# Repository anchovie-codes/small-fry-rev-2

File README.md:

# small-fry-rev-2
a keyboard with a fishy layout. now with better mods and a funky pcb!

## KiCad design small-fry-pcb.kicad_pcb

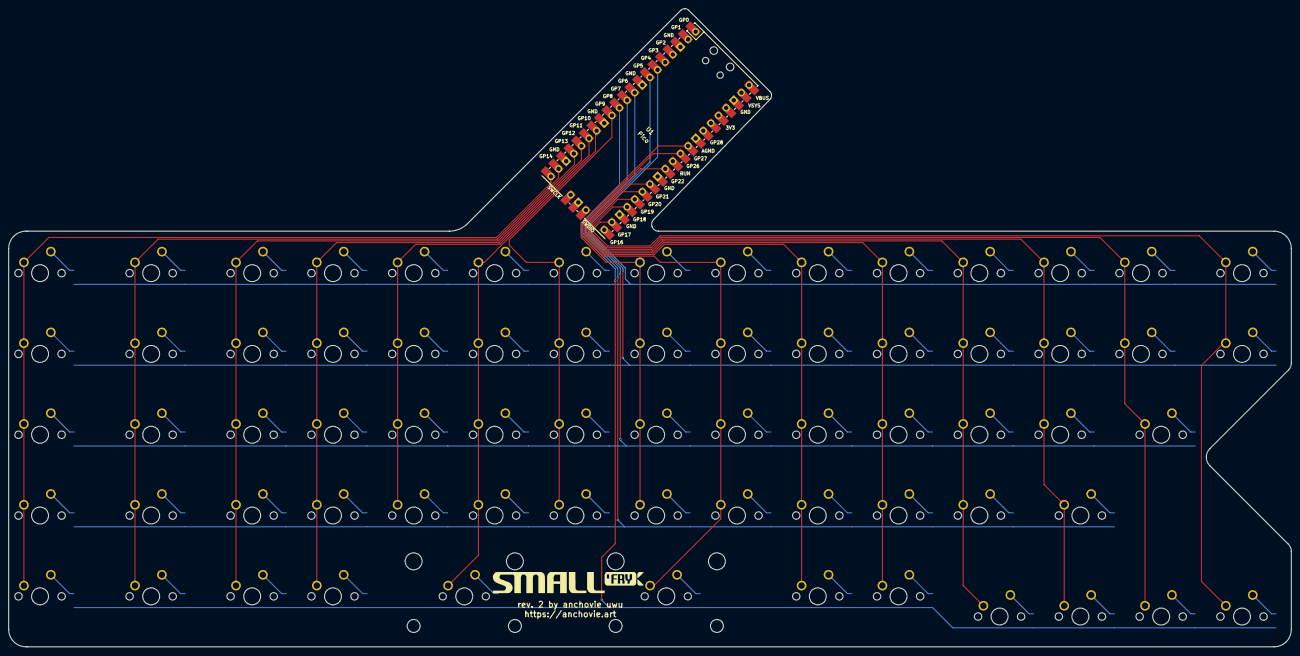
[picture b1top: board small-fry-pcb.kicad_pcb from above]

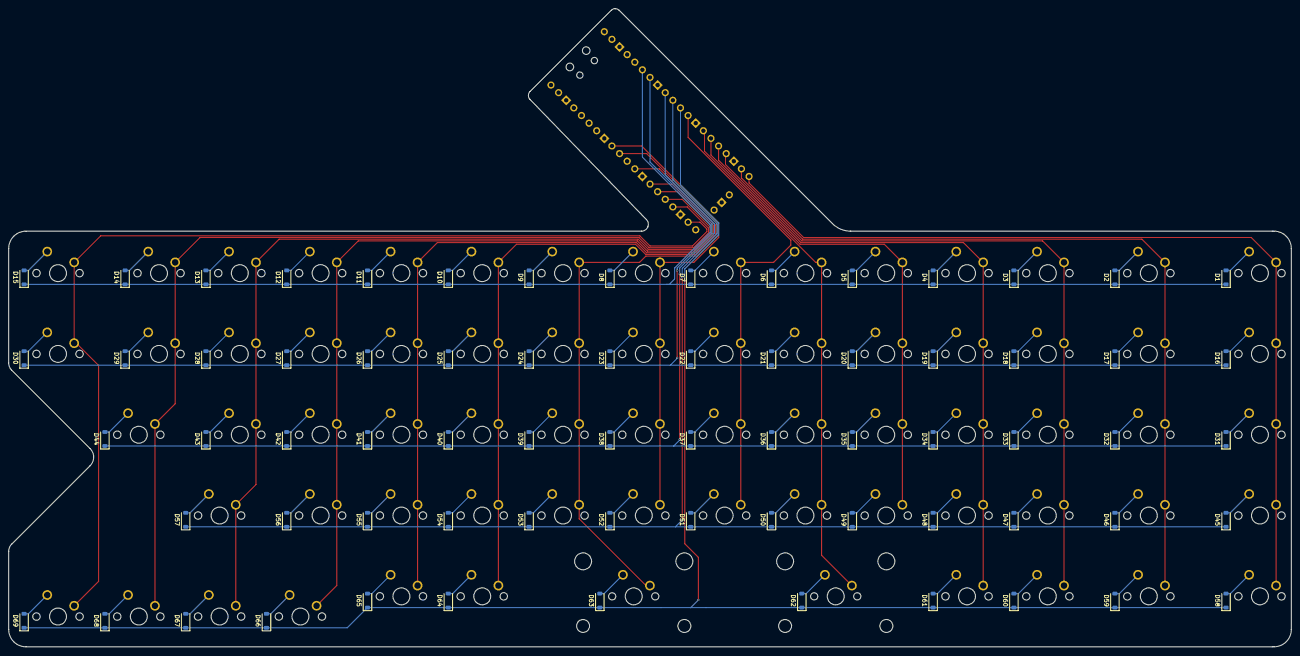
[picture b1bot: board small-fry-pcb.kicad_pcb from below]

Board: 2 copper layers, 302.4 x 150.5 mm, 139 parts (69 on the bottom side), 89 nets.

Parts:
D1, D2, D3, D4, D5, D6, D7, D8, D9, D10, D11, D12, D13, D14, D15, D16, D17, D18, D19, D20, D21, D22, D23, D24, D25, D26, D27, D28, D29, D30, D31, D32, D33, D34, D35, D36, D37, D38, D39, D40, D41, D42, D43, D44, D45, D46, D47, D48, D49, D50, D51, D52, D53, D54, D55, D56, D57, D58, D59, D60, D61, D62, D63, D64, D65, D66, D67, D68, D69: D_Small; D_SOD-123
MX1, MX16, MX31, MX45, MX58: MX-NoLED; SW_MX_1.25u
MX2, MX15, MX17, MX30, MX32, MX44, MX46, MX57, MX59: MX-NoLED; SW_MX_1.5u
MX3, MX4, MX5, MX6, MX7, MX8, MX9, MX10, MX11, MX12, MX13, MX14, MX18, MX19, MX20, MX21, MX22, MX23, MX24, MX25, MX26, MX27, MX28, MX29, MX33, MX34, MX35, MX36, MX37, MX38, MX39, MX40, MX41, MX42, MX43, MX47, MX48, MX49, MX50, MX51, MX52, MX53, MX54, MX55, MX56, MX60, MX61, MX64, MX65, MX66, MX67, MX68, MX69: MX-NoLED; SW_MX_1u
MX62: MX-NoLED; MX-Solderable-2.25U-ReversedStabilizers
MX63: MX-NoLED; MX-Solderable-2.75U-ReversedStabilizers
U1: Pico; RPi_Pico_SMD_TH

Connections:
unnamed: D1.2 (A), MX1.2 (ROW)
unnamed: D2.2 (A), MX2.2 (ROW)
unnamed: D3.2 (A), MX3.2 (ROW)
unnamed: D4.2 (A), MX4.2 (ROW)
unnamed: D5.2 (A), MX5.2 (ROW)
unnamed: D6.2 (A), MX6.2 (ROW)
unnamed: D7.2 (A), MX7.2 (ROW)
unnamed: D8.2 (A), MX8.2 (ROW)
unnamed: D9.2 (A), MX9.2 (ROW)
unnamed: D10.2 (A), MX10.2 (ROW)
unnamed: D11.2 (A), MX11.2 (ROW)
unnamed: D12.2 (A), MX12.2 (ROW)
unnamed: D13.2 (A), MX13.2 (ROW)
unnamed: D14.2 (A), MX14.2 (ROW)
unnamed: D15.2 (A), MX15.2 (ROW)
unnamed: D16.2 (A), MX16.2 (ROW)
unnamed: D17.2 (A), MX17.2 (ROW)
unnamed: D18.2 (A), MX18.2 (ROW)
unnamed: D19.2 (A), MX19.2 (ROW)
unnamed: D20.2 (A), MX20.2 (ROW)
unnamed: D21.2 (A), MX21.2 (ROW)
unnamed: D22.2 (A), MX22.2 (ROW)
unnamed: D23.2 (A), MX23.2 (ROW)
unnamed: D24.2 (A), MX24.2 (ROW)
unnamed: D25.2 (A), MX25.2 (ROW)
unnamed: D26.2 (A), MX26.2 (ROW)
unnamed: D27.2 (A), MX27.2 (ROW)
unnamed: D28.2 (A), MX28.2 (ROW)
unnamed: D29.2 (A), MX29.2 (ROW)
unnamed: D30.2 (A), MX30.2 (ROW)
unnamed: D31.2 (A), MX31.2 (ROW)
unnamed: D32.2 (A), MX32.2 (ROW)
unnamed: D33.2 (A), MX33.2 (ROW)
unnamed: D34.2 (A), MX34.2 (ROW)
unnamed: D35.2 (A), MX35.2 (ROW)
unnamed: D36.2 (A), MX36.2 (ROW)
unnamed: D37.2 (A), MX37.2 (ROW)
unnamed: D38.2 (A), MX38.2 (ROW)
unnamed: D39.2 (A), MX39.2 (ROW)
unnamed: D40.2 (A), MX40.2 (ROW)
unnamed: D41.2 (A), MX41.2 (ROW)
unnamed: D42.2 (A), MX42.2 (ROW)
unnamed: D43.2 (A), MX43.2 (ROW)
unnamed: D44.2 (A), MX44.2 (ROW)
unnamed: D45.2 (A), MX45.2 (ROW)
unnamed: D46.2 (A), MX46.2 (ROW)
unnamed: D47.2 (A), MX47.2 (ROW)
unnamed: D48.2 (A), MX48.2 (ROW)
unnamed: D49.2 (A), MX49.2 (ROW)
unnamed: D50.2 (A), MX50.2 (ROW)
unnamed: D51.2 (A), MX51.2 (ROW)
unnamed: D52.2 (A), MX52.2 (ROW)
unnamed: D53.2 (A), MX53.2 (ROW)
unnamed: D54.2 (A), MX54.2 (ROW)
unnamed: D55.2 (A), MX55.2 (ROW)
unnamed: D56.2 (A), MX56.2 (ROW)
unnamed: D57.2 (A), MX57.2 (ROW)
unnamed: D58.2 (A), MX58.2 (ROW)
unnamed: D59.2 (A), MX59.2 (ROW)
unnamed: D60.2 (A), MX60.2 (ROW)
unnamed: D61.2 (A), MX61.2 (ROW)
unnamed: D62.2 (A), MX62.2 (ROW)
unnamed: D63.2 (A), MX63.2 (ROW)
unnamed: D64.2 (A), MX64.2 (ROW)
unnamed: D65.2 (A), MX65.2 (ROW)
unnamed: D66.2 (A), MX66.2 (ROW)
unnamed: D67.2 (A), MX67.2 (ROW)
unnamed: D68.2 (A), MX68.2 (ROW)
unnamed: D69.2 (A), MX69.2 (ROW)
col0: MX1.1 (COL), MX16.1 (COL), MX31.1 (COL), MX45.1 (COL), MX58.1 (COL), U1.20 (GPIO15)
col1: MX2.1 (COL), MX17.1 (COL), MX32.1 (COL), MX46.1 (COL), MX59.1 (COL), U1.19 (GPIO14)
col2: MX3.1 (COL), MX18.1 (COL), MX33.1 (COL), MX47.1 (COL), MX60.1 (COL), U1.17 (GPIO13)
col3: MX4.1 (COL), MX19.1 (COL), MX34.1 (COL), MX48.1 (COL), MX61.1 (COL), U1.16 (GPIO12)
col4: MX5.1 (COL), MX20.1 (COL), MX35.1 (COL), MX49.1 (COL), U1.15 (GPIO11)
col5: MX6.1 (COL), MX21.1 (COL), MX36.1 (COL), MX50.1 (COL), MX62.1 (COL), U1.14 (GPIO10)
col6: MX7.1 (COL), MX22.1 (COL), MX37.1 (COL), MX51.1 (COL), U1.12 (GPIO9)
col7: MX8.1 (COL), MX23.1 (COL), MX38.1 (COL), MX52.1 (COL), U1.32 (GPIO27_ADC1)
col8: MX9.1 (COL), MX24.1 (COL), MX39.1 (COL), MX53.1 (COL), MX63.1 (COL), U1.31 (GPIO26_ADC0)
col9: MX10.1 (COL), MX25.1 (COL), MX40.1 (COL), MX54.1 (COL), MX64.1 (COL), U1.29 (GPIO22)
col10: MX11.1 (COL), MX26.1 (COL), MX41.1 (COL), MX55.1 (COL), MX65.1 (COL), U1.27 (GPIO21)
col11: MX12.1 (COL), MX27.1 (COL), MX42.1 (COL), MX56.1 (COL), MX66.1 (COL), U1.26 (GPIO20)
col12: MX13.1 (COL), MX28.1 (COL), MX43.1 (COL), MX57.1 (COL), MX67.1 (COL), U1.25 (GPIO19)
col13: MX14.1 (COL), MX29.1 (COL), MX44.1 (COL), MX68.1 (COL), U1.24 (GPIO18)
col14: MX15.1 (COL), MX30.1 (COL), MX69.1 (COL), U1.22 (GPIO17)
row0: D1.1 (K), D2.1 (K), D3.1 (K), D4.1 (K), D5.1 (K), D6.1 (K), D7.1 (K), D8.1 (K), D9.1 (K), D10.1 (K), D11.1 (K), D12.1 (K), D13.1 (K), D14.1 (K), D15.1 (K), U1.6 (GPIO4)
row1: D16.1 (K), D17.1 (K), D18.1 (K), D19.1 (K), D20.1 (K), D21.1 (K), D22.1 (K), D23.1 (K), D24.1 (K), D25.1 (K), D26.1 (K), D27.1 (K), D28.1 (K), D29.1 (K), D30.1 (K), U1.7 (GPIO5)
row2: D31.1 (K), D32.1 (K), D33.1 (K), D34.1 (K), D35.1 (K), D36.1 (K), D37.1 (K), D38.1 (K), D39.1 (K), D40.1 (K), D41.1 (K), D42.1 (K), D43.1 (K), D44.1 (K), U1.9 (GPIO6)
row3: D45.1 (K), D46.1 (K), D47.1 (K), D48.1 (K), D49.1 (K), D50.1 (K), D51.1 (K), D52.1 (K), D53.1 (K), D54.1 (K), D55.1 (K), D56.1 (K), D57.1 (K), U1.10 (GPIO7)
row4: D58.1 (K), D59.1 (K), D60.1 (K), D61.1 (K), D62.1 (K), D63.1 (K), D64.1 (K), D65.1 (K), D66.1 (K), D67.1 (K), D68.1 (K), D69.1 (K), U1.11 (GPIO8)

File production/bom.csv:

Designator,Footprint,Quantity,Value,LCSC Part #
"D1, D10, D11, D12, D13, D14, D15, D16, D17, D18, D19, D2, D20, D21, D22, D23, D24, D25, D26, D27, D28, D29, D3, D30, D31, D32, D33, D34, D35, D36, D37, D38, D39, D4, D40, D41, D42, D43, D44, D45, D46, D47, D48, D49, D5, D50, D51, D52, D53, D54, D55, D56, D57, D58, D59, D6, D60, D61, D62, D63, D64, D65, D66, D67, D68, D69, D7, D8, D9",D_SOD-123,69,D_Small,
"MX1, MX16, MX31, MX45, MX58",SW_MX_1.25u,5,MX-NoLED,
"MX10, MX11, MX12, MX13, MX14, MX18, MX19, MX20, MX21, MX22, MX23, MX24, MX25, MX26, MX27, MX28, MX29, MX3, MX33, MX34, MX35, MX36, MX37, MX38, MX39, MX4, MX40, MX41, MX42, MX43, MX47, MX48, MX49, MX5, MX50, MX51, MX52, MX53, MX54, MX55, MX56, MX6, MX60, MX61, MX64, MX65, MX66, MX67, MX68, MX69, MX7, MX8, MX9",SW_MX_1u,53,MX-NoLED,
"MX15, MX17, MX2, MX30, MX32, MX44, MX46, MX57, MX59",SW_MX_1.5u,9,MX-NoLED,
MX62,MX-Solderable-2.25U-ReversedStabilizers,1,MX-NoLED,
MX63,MX-Solderable-2.75U-ReversedStabilizers,1,MX-NoLED,
U1,RPi_Pico_SMD_TH,1,Pico,

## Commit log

2024-09-27 updated footprints, rotated mcu
2024-09-28 made it a fish
2024-09-28 fixed cols
2024-09-28 fixed rows, generated gerbers
2024-11-11 updated edge cuts and gerbers
2024-11-11 Squashed commit of the following:
    commit e493926800ae8eeeb9c8551a418d401659cc4f4a
    Author: anchovie-codes <littlebrother.free@gmail.com>
    Date: Sun Nov 10 19:39:24 2024 -0500
    updated edge cuts and gerbers
    commit a852bf54e9e750d94bc40db8a16316f7cdac5ac1
    Author: anchovie-codes <littlebrother.free@gmail.com>
2024-11-11 added bom and prod files
2024-11-22 updated and compiled firmware
2025-01-14 added bent case files
